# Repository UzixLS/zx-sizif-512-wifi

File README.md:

## WiFi module for Sizif-512

For software see [here](https://github.com/nihirash/zx-net-tools)

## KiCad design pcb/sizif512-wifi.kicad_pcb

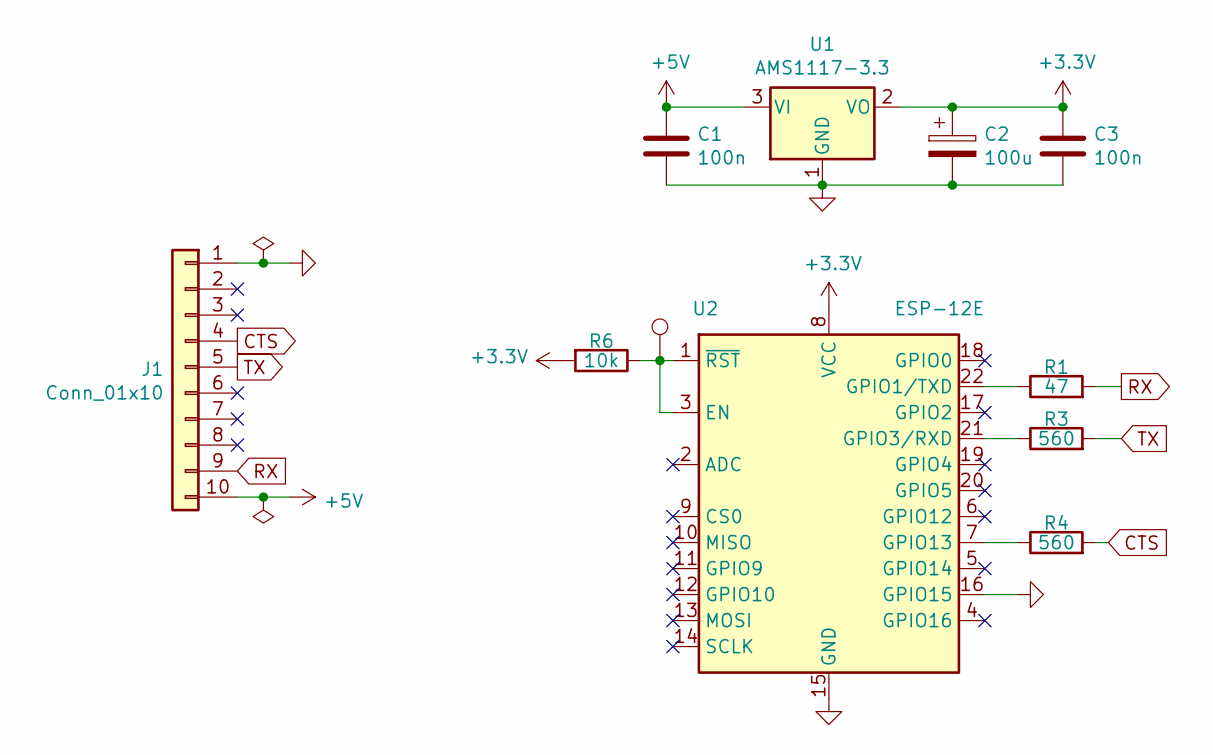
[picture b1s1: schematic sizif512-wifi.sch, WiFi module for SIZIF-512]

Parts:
C1, C3: 100n; C_0805_2012Metric_Pad1.15x1.40mm_HandSolder
C2: 100u; CP_EIA-6032-15_Kemet-U_Pad2.25x2.35mm_HandSolder
J1: Conn_01x10; PinSocket_1x10_P2.54mm_Vertical
R1: 47; C_0805_2012Metric_Pad1.15x1.40mm_HandSolder
R3, R4: 560; C_0805_2012Metric_Pad1.15x1.40mm_HandSolder
R6: 10k; C_0805_2012Metric_Pad1.15x1.40mm_HandSolder
TP1: TestPoint; Pin_D0.7mm_L6.5mm_W1.8mm_FlatFork
U1: AMS1117-3.3; SOT-223-3_TabPin2
U2: ESP-12E

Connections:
+3V3: C2.1, C3.1, R6.2, U1.2 (VO), U2.8 (VCC)
+5V: C1.1, J1.10, U1.3 (VI)
CTS: J1.4, R4.2
GND: C1.2, C2.2, C3.2, J1.1, U1.1 (GND), U2.15 (GND), U2.16 (GPIO15)
unnamed: R1.1, U2.22 (GPIO1/TXD)
unnamed: R3.1, U2.21 (GPIO3/RXD)
unnamed: R4.1, U2.7 (GPIO13)
unnamed: R6.1, TP1.1, U2.1 (~RST), U2.3 (EN)
RX: J1.9, R1.2
TX: J1.5, R3.2

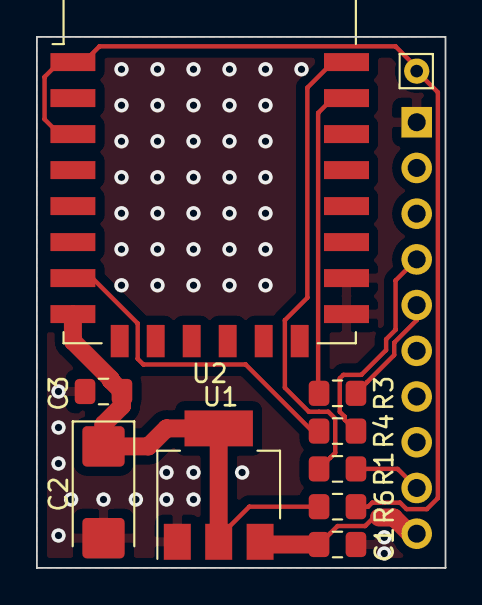
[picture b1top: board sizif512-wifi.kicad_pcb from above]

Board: 2 copper layers, 22.7 x 29.5 mm, 11 parts (1 on the bottom side), 10 nets.

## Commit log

2020-07-06 initial
2020-07-06 import rev.A files
2020-07-06 import rev B files
2020-07-29 fix github language detector
2021-02-27 import rev C files
